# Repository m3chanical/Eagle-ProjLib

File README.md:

# Eagle-ProjLib
Projects and component libraries created in Eagle

### Atmel ARM MCU: 
*	Build Schematic

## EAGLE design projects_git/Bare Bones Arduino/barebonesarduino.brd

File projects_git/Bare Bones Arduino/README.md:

This project is titled bare bones arduino because I initially followed a Sparkfun tutorial. 
I changed mine up a bunch and added a 2x4 female header so that an NRF24 radio can be attached.

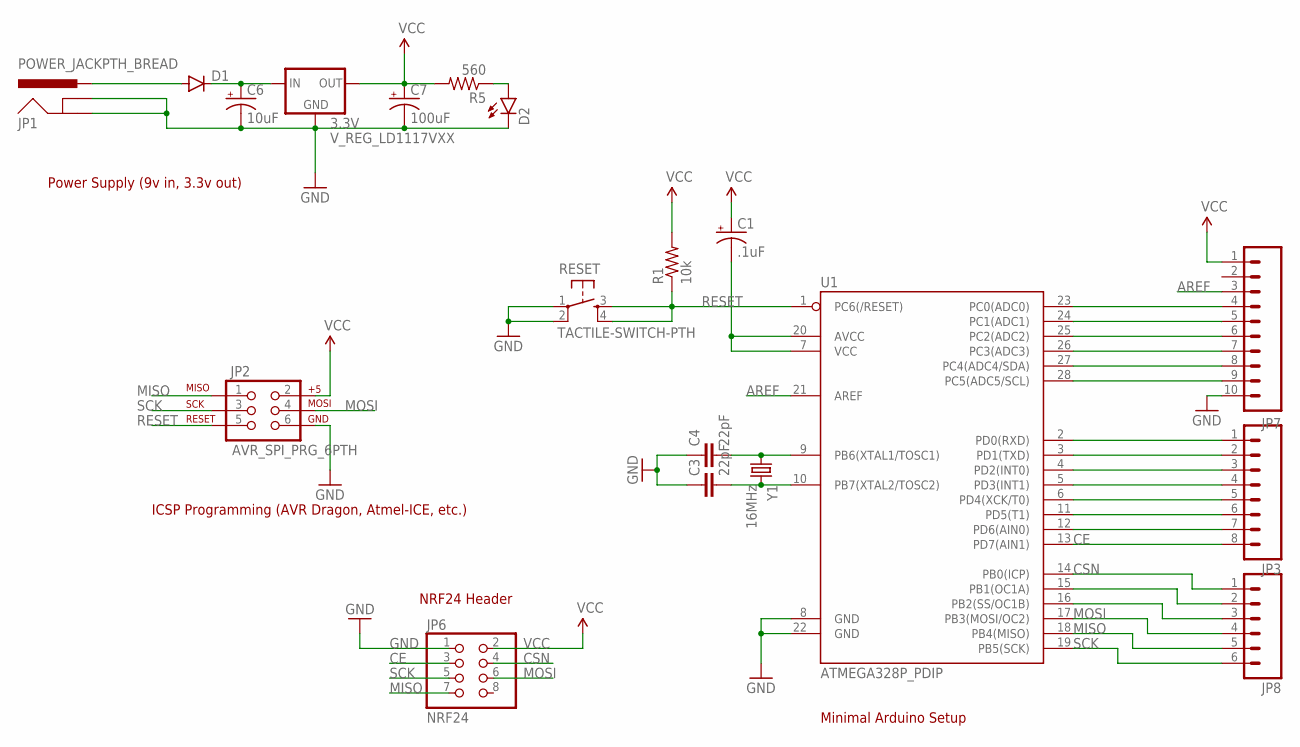
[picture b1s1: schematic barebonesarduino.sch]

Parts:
3.3V: V_REG_LD1117VXX; 78XXL
C1: .1uF; CPOL-RADIAL-100UF-25V
C3, C4: 22pF; CAP-PTH-SMALL
C6: 10uF; CPOL-RADIAL-100UF-25V
C7: 100uF; CPOL-RADIAL-100UF-25V
D1: DIODEPTH; DIODE-1N4001
D2: LED5MM
JP1: POWER_JACKPTH_BREAD; POWER_JACK_PTH_BREAD
JP2: AVR_SPI_PRG_6PTH; 2X3
JP3: M08NO_SILK_FEMALE_PTH; 1X08_NO_SILK
JP6: NRF24; 2X04
JP7: M10NO_SILK_PTH_FEMALE; 1X10_NO_SILK
JP8: M06NO_SILK_YES_STOP; 1X06_NO_SILK_YES_STOP
R1: 10k; AXIAL-0.4
R5: 560; AXIAL-0.4
RESET: TACTILE-SWITCH-PTH; TAC-SWITCH-PTH
U1: ATMEGA328P_PDIP; DIL28-3
Y1: 16MHz; HC49US

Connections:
AREF: JP7.3, U1.21 (AREF)
CE: JP3.8, JP6.3, U1.13 (PD7(AIN1))
CSN: JP6.4, JP8.1, U1.14 (PB0(ICP))
GND: 3.3V.IN (GND), C3.1, C4.1, C6.2 (-), C7.2 (-), D2.K (C), JP1.GND, JP1.GNDBREAK, JP2.6, JP6.1, JP7.10, RESET.1, RESET.2, U1.8 (GND), U1.22 (GND)
MISO: JP2.1, JP6.7, JP8.5, U1.18 (PB4(MISO))
MOSI: JP2.4, JP6.6, JP8.4, U1.17 (PB3(MOSI/OC2))
unnamed: C4.2, U1.9 (PB6(XTAL1/TOSC1)), Y1.1
unnamed: JP7.4, U1.23 (PC0(ADC0))
unnamed: JP7.5, U1.24 (PC1(ADC1))
unnamed: JP7.6, U1.25 (PC2(ADC2))
unnamed: JP7.7, U1.26 (PC3(ADC3))
unnamed: JP7.8, U1.27 (PC4(ADC4/SDA))
unnamed: JP7.9, U1.28 (PC5(ADC5/SCL))
unnamed: C3.2, U1.10 (PB7(XTAL2/TOSC2)), Y1.2
unnamed: JP3.1, U1.2 (PD0(RXD))
unnamed: JP3.2, U1.3 (PD1(TXD))
unnamed: JP3.3, U1.4 (PD2(INT0))
unnamed: JP3.4, U1.5 (PD3(INT1))
unnamed: JP3.5, U1.6 (PD4(XCK/T0))
unnamed: JP3.6, U1.11 (PD5(T1))
unnamed: 3.3V.OUT (IN), C6.1 (+), D1.C
unnamed: D1.A, JP1.PWR
unnamed: D2.A, R5.P$1 (1)
unnamed: JP3.7, U1.12 (PD6(AIN0))
unnamed: C1.2 (-), U1.7 (VCC), U1.20 (AVCC)
unnamed: JP8.2, U1.15 (PB1(OC1A))
unnamed: JP8.3, U1.16 (PB2(SS/OC1B))
RESET: JP2.5, R1.P$1 (1), RESET.3, RESET.4, U1.1 (PC6(/RESET))
SCK: JP2.3, JP6.5, JP8.6, U1.19 (PB5(SCK))
VCC: 3.3V.GND (OUT), C1.1 (+), C7.1 (+), JP2.2, JP6.2, JP7.1, R1.P$2 (2), R5.P$2 (2)

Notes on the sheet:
NRF24 Header
ICSP Programming (AVR Dragon, Atmel-ICE, etc.)
Power Supply (9v in, 3.3v out)
Minimal Arduino Setup

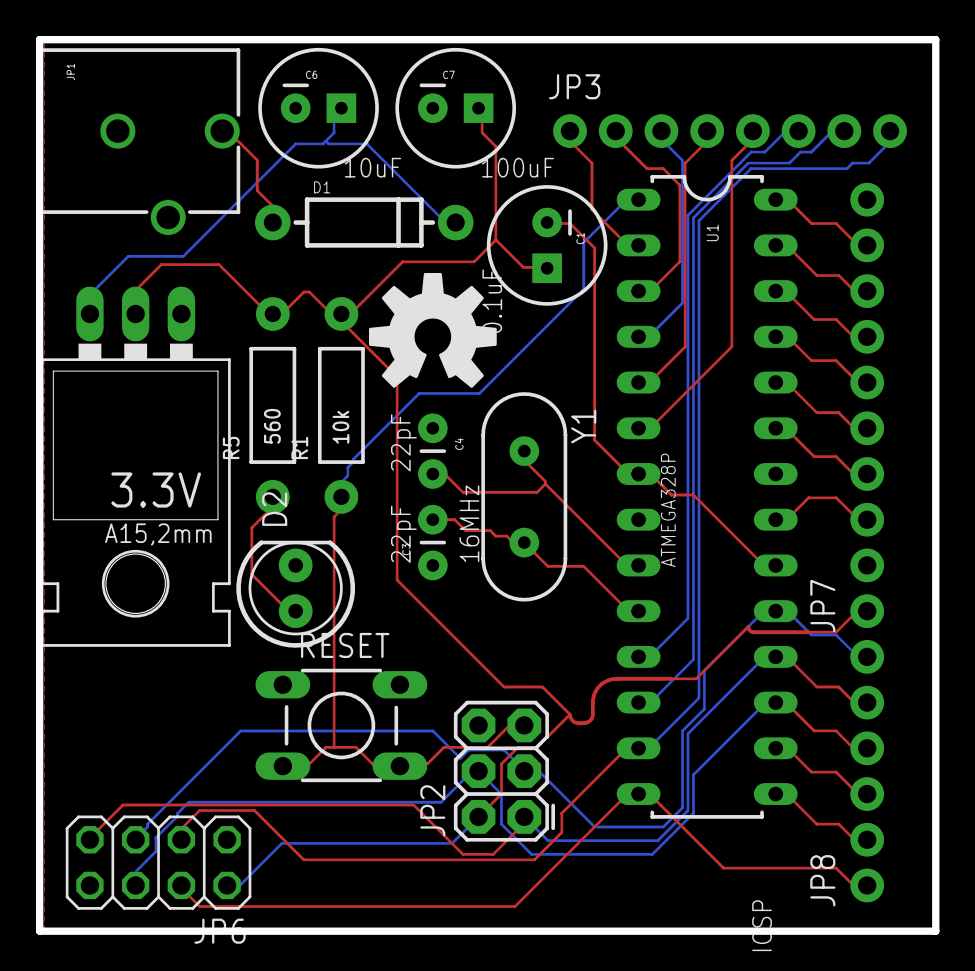
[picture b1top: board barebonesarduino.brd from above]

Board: 2 copper layers, 49.8 x 49.5 mm, 20 parts (0 on the bottom side), 30 nets.

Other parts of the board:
U$1: OSHW-LOGO-L

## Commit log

2016-03-27 set up basic skeleton. libraries obtained from femtoduino
2016-03-27 change git settings, test
2016-03-27 add other projects to git
2016-03-27 Create README.md
    seeing if other folders display a readme.

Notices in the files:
parts and their libraries:
SparkFun-Capacitors: Licensing: Creative Commons ShareAlike 4.0 International - https://creativecommons.org/licenses/by-sa/4.0
